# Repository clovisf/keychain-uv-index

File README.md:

# keychain-uv-index
 
A keychain-sized UV index indicator, showing the UV index number by blinking a LED accordingly. Attiny85 controller and CR2032 battery. https://fritzenlab.net

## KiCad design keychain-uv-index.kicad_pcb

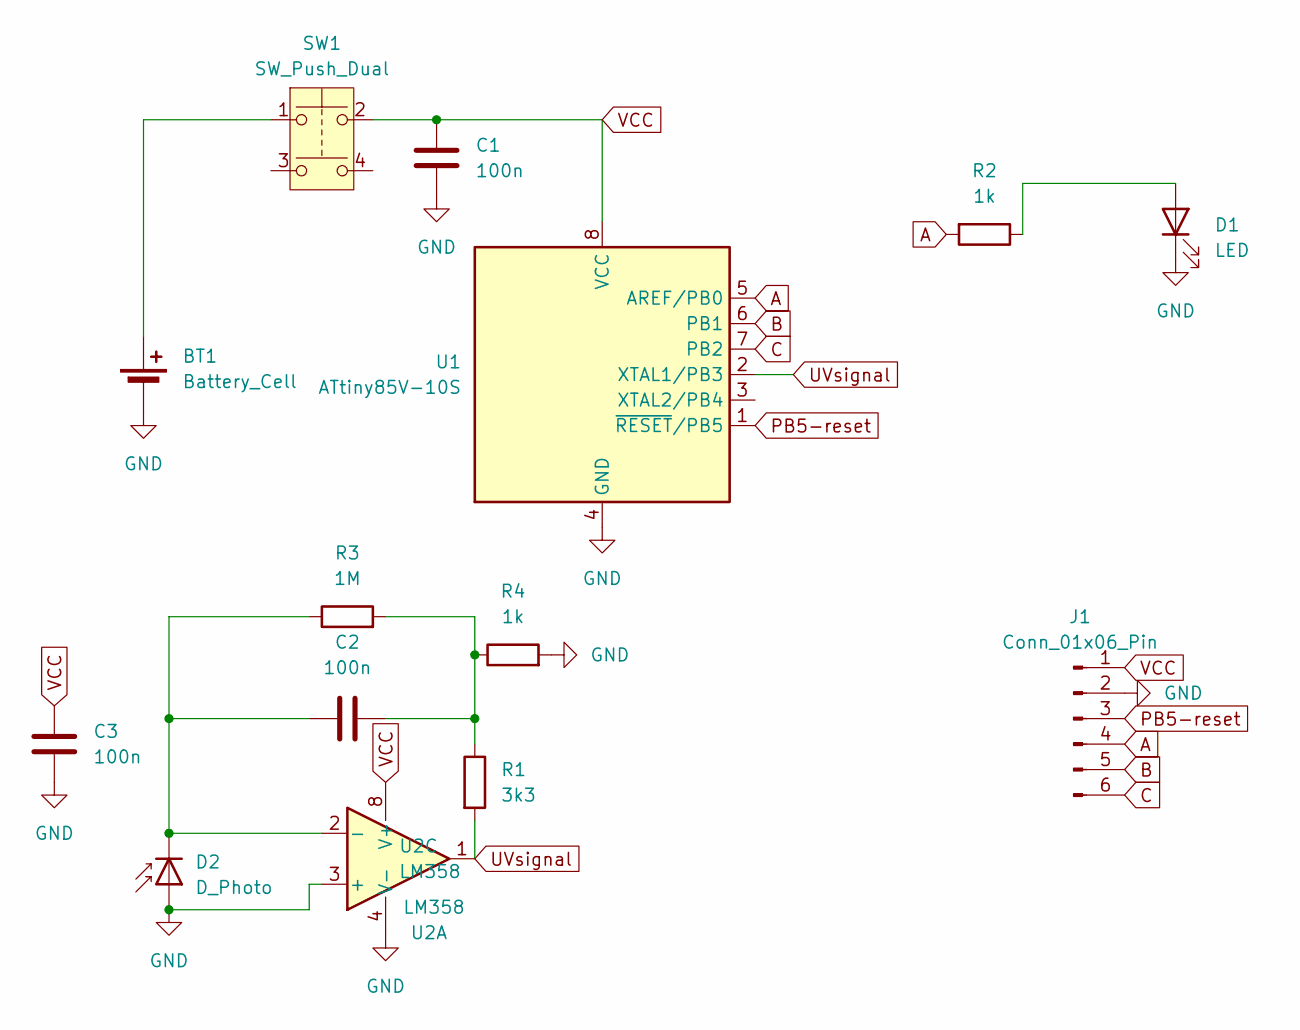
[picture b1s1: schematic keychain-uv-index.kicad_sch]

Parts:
BT1: Battery_Cell; Battery_Panasonic_CR2032-HFN_Horizontal_CircularHoles
C1, C2, C3: 100n; C_0805_2012Metric
D1: LED; LED_0805_2012Metric
D2: D_Photo; LED_PLCC-2_3.4x3.0mm_AK
J1: Conn_01x06_Pin; PinHeader_1x06_P2.54mm_Vertical
R1: 3k3; R_0805_2012Metric
R2, R4: 1k; R_0805_2012Metric
R3: 1M; R_0805_2012Metric
SW1: SW_Push_Dual; SW_SPST_PTS810
U1: ATtiny85V-10S; SOIC-8W_5.3x5.3mm_P1.27mm
U2: LM358; SOIC-8W_5.3x5.3mm_P1.27mm

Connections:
A: J1.4, R2.2, U1.5 (AREF/PB0)
B: J1.5, U1.6 (PB1)
C: J1.6, U1.7 (PB2)
GND: BT1.2 (-), C1.2, C3.1, D1.1 (K), D2.2 (A), J1.2, R4.2, U1.4 (GND), U2.3 (+), U2.4 (V-)
unnamed: BT1.1 (+), SW1.1
unnamed: C2.2, R1.1, R3.2, R4.1
unnamed: D1.2 (A), R2.1
unnamed: C2.1, D2.1 (K), R3.1, U2.2 (-)
PB5-reset: J1.3, U1.1 (~RESET/PB5)
UVsignal: R1.2, U1.2 (XTAL1/PB3), U2.1
VCC: C1.1, C3.2, J1.1, SW1.2, U1.8 (VCC), U2.8 (V+)

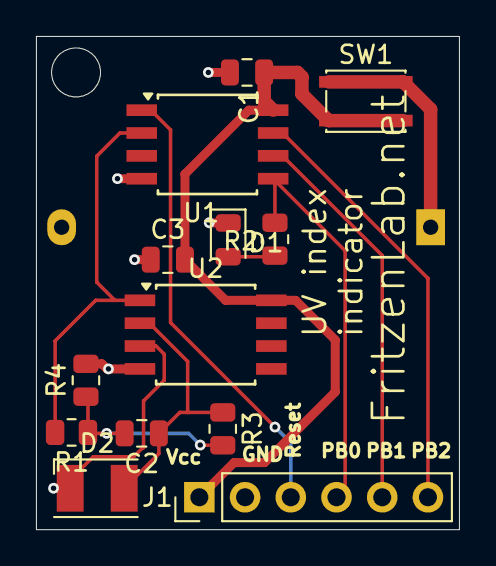
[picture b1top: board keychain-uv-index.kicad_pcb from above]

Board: 2 copper layers, 23.5 x 27.4 mm, 14 parts (1 on the bottom side), 11 nets.

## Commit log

2024-10-18 added files
2024-10-18 renamed files
2024-10-18 edited schematics
2024-10-19 finished PCB design
2024-10-21 backups
2024-11-23 initial code commit
2024-11-23 created code
